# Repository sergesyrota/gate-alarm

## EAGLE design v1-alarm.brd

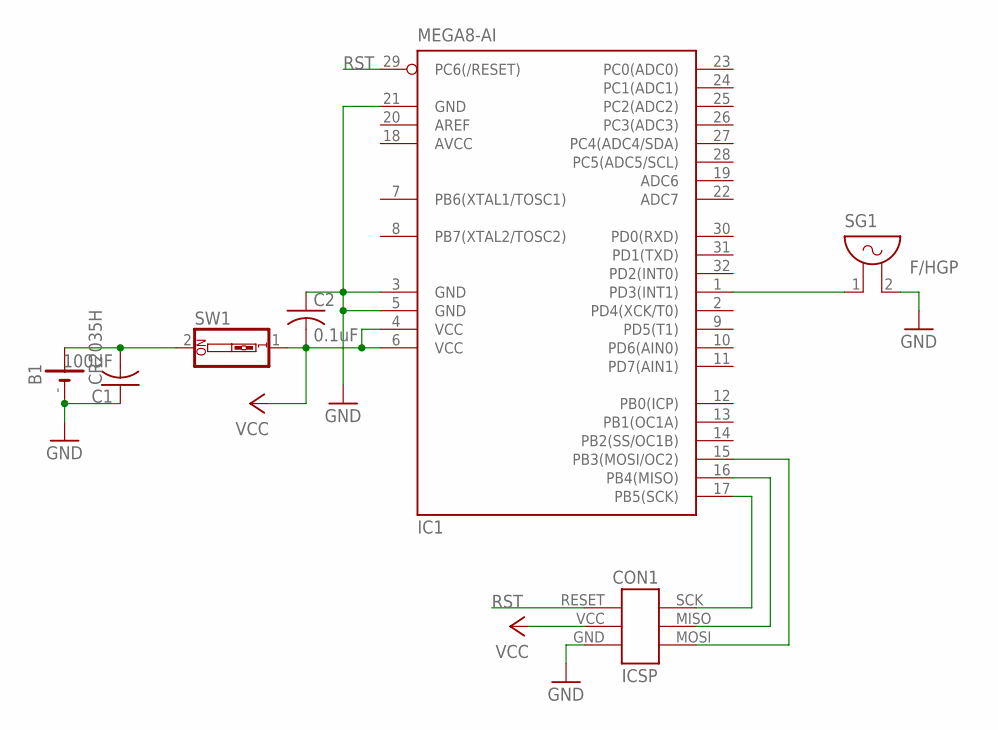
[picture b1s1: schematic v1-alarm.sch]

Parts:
B1: CR2035H; CR2032H
C1: 100uF; C2220K
C2: 0.1uF; C0603
CON1: ICSP-HEADER
IC1: MEGA8-AI; TQFP32-08
SG1: F/HGP
SW1: SW_DIP-1; EDG-01

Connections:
AVCC: IC1.18 (AVCC)
GND: B1.-, C1.1, C2.1, CON1.GND, IC1.3 (GND), IC1.5 (GND), IC1.21 (GND), SG1.2
unnamed: CON1.SCK, IC1.17 (PB5(SCK))
unnamed: CON1.MISO, IC1.16 (PB4(MISO))
unnamed: CON1.MOSI, IC1.15 (PB3(MOSI/OC2))
unnamed: B1.+, C1.2, SW1.2
unnamed: IC1.1 (PD3(INT1)), SG1.1
RST: CON1.RESET, IC1.29 (PC6(/RESET))
VCC: C2.2, CON1.VCC (+5V), IC1.4 (VCC), IC1.6 (VCC), SW1.1

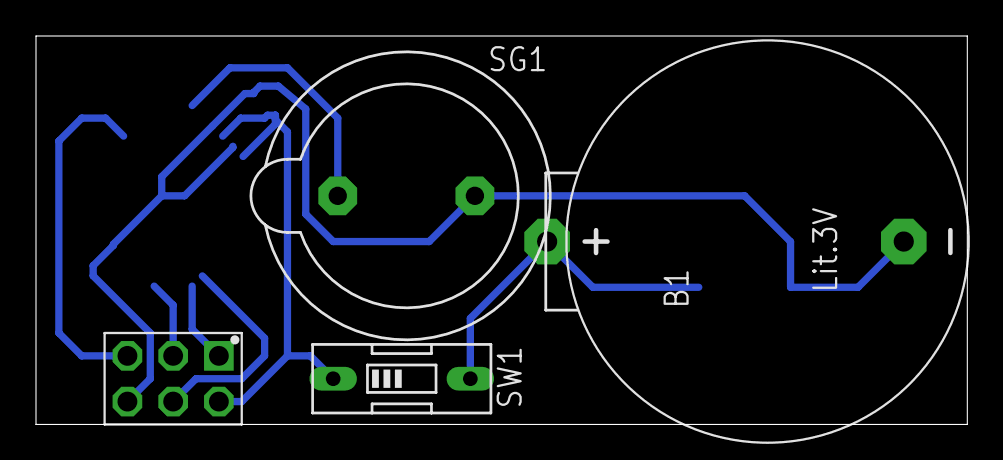
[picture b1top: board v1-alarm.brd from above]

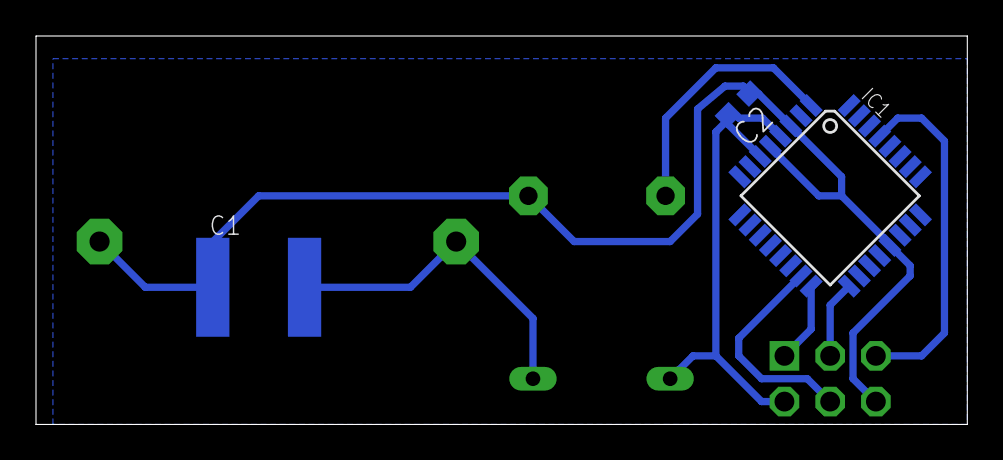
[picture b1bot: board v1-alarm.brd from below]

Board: 2 copper layers, 51.7 x 21.6 mm, 7 parts (3 on the bottom side), 8 nets.

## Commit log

2015-04-26 Initial commit with board design and sketch.
